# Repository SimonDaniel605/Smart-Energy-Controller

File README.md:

# Smart-Energy-Controller
A modular STM32-based smart energy monitoring and load control system with wireless connectivity, real-time power measurement, and remote switching.

## Overview

The Smart Energy Controller enables real-time monitoring of electrical consumption and wireless control of connected loads. The system is designed to support intelligent energy management through distributed monitoring, remote switching and centralised control.

- **Energy Monitoring:** Measurement of voltage, current, power, power factor and energy consumption.
- **Remote Switching:** Wireless control of connected electrical loads.
- **Real-Time Data:** Continuous transmission of electrical measurements.
- **Energy Management:** Automated load scheduling and power consumption optimisation.
- **Scalability:** Multiple controllers connected to a central monitoring system.
- **Remote Access:** Monitoring and control through a mobile device.

## Project Structure

```text
Smart-Energy-Controller/
├── Docs/
├── Firmware/
└── Hardware/
```

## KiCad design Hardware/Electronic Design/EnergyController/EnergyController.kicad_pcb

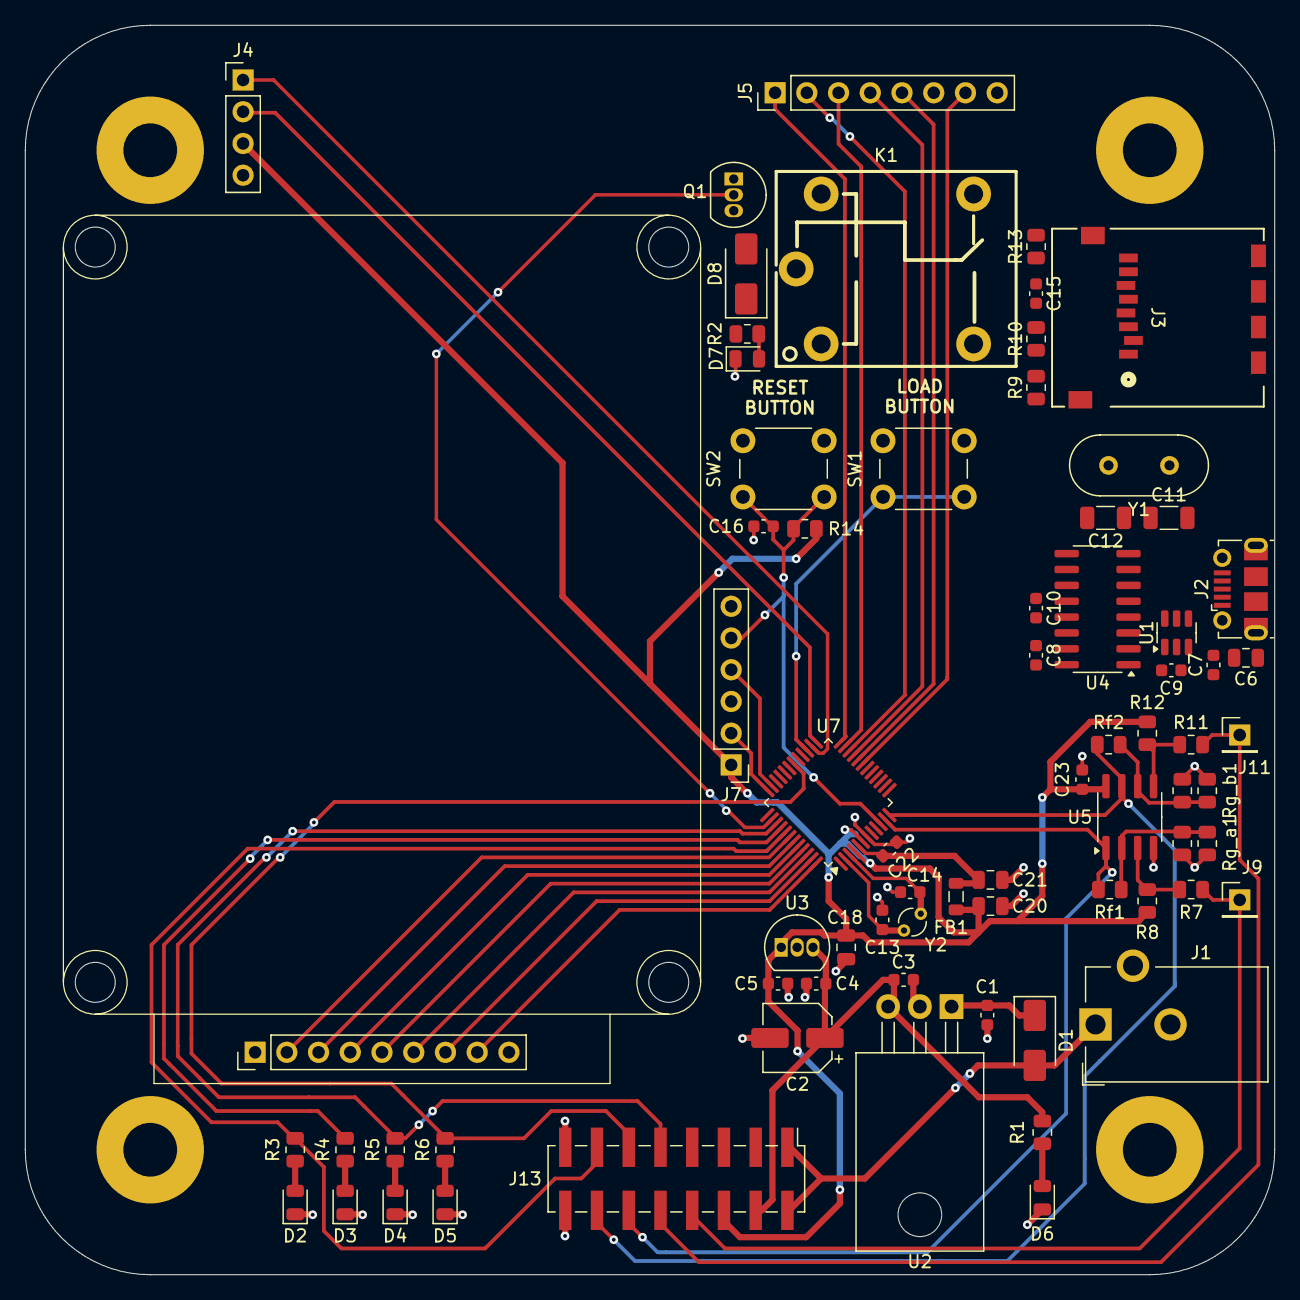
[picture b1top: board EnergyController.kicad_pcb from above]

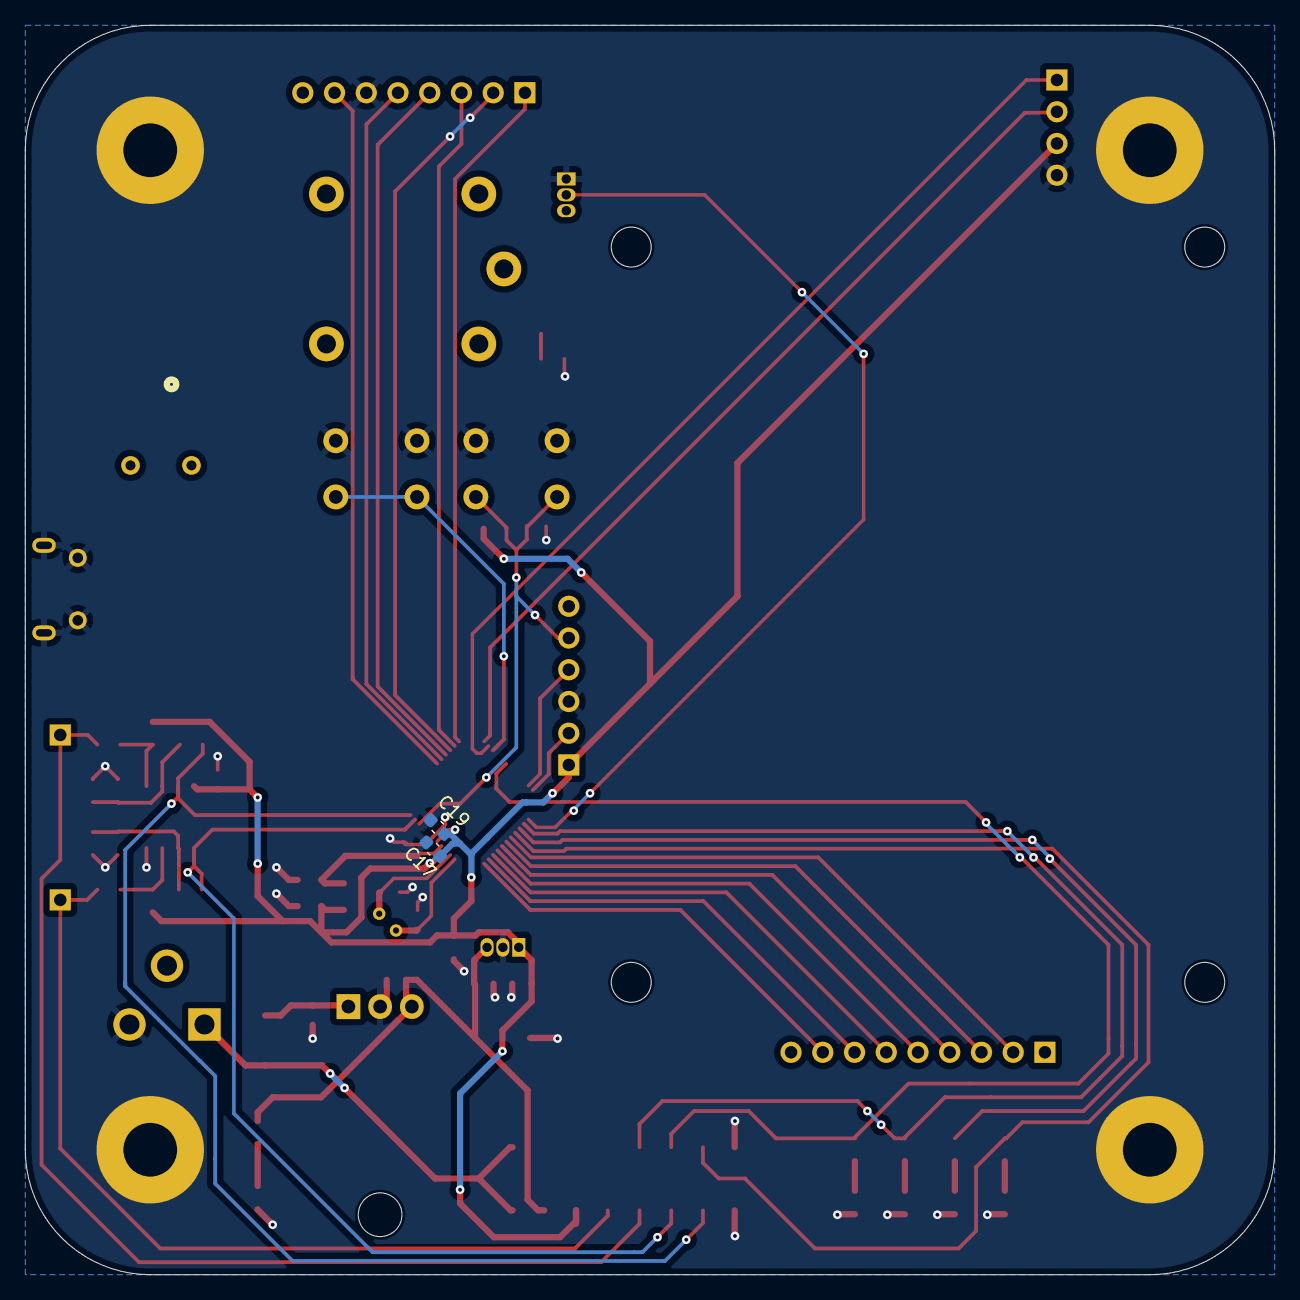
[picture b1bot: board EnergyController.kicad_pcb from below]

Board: 2 copper layers, 100.0 x 100.0 mm, 82 parts (2 on the bottom side), 61 nets.

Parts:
C1, C3, C4, C5, C7, C8, C9, C10, C15, C16, C17, C19, C23: 100n; C_0603_1608Metric
C2: 10u; CP_Elec_5x5.4
C6, C18: 10u; C_0805_2012Metric
C11, C12: 22p; C_1206_3216Metric
C13, C14: 20p; C_0603_1608Metric
C20, C21: 1u; C_0805_2012Metric
C22: 10n; C_0603_1608Metric
D1, D8: 1N4007; D_SMA
D2, D3, D4, D5, D6, D7: LED; LED_0805_2012Metric
FB1: 120R; L_0805_2012Metric
H1, H2, H3, H4: MountingHole_Pad; MountingHole_4.3mm_M4_Pad
H5, H6, H7, H8: MountingHole; MountingHole_3.2mm_M3
J1: Barrel_Jack; BarrelJack_CUI_PJ-102AH_Horizontal
J2: USB_OTG; USB_Micro-B_Molex-105017-0001
J3: 112A-TAAR-R03; CONN8_-TAAR-R03_ATT
J4: Conn_01x04_Pin; PinHeader_1x04_P2.54mm_Vertical
J5: Conn_01x08_Pin; PinHeader_1x08_P2.54mm_Vertical
J6: Conn_01x09_Pin; PinHeader_1x09_P2.54mm_Vertical
J7: Conn_01x06_Pin; PinHeader_1x06_P2.54mm_Vertical
J9, J11: Conn_01x01_Pin; PinHeader_1x01_P2.54mm_Vertical
J13: Conn_02x08; PinHeader_2x08_P2.54mm_Vertical_SMD
K1: Relay_SPDT; RELAY-TH_SRD-XXVDC-XL-C
Q1: 2N7000; TO-92_Inline
R1, R2, R3, R4, R5, R6: R; R_0805_2012Metric
R7, R11, R14: 10k; R_0805_2012Metric
R8, R12: 33k; R_0805_2012Metric
R9, R10, R13: 100k; R_0805_2012Metric
Rf1, Rf2: 10k; R_0805_2012Metric
Rg_a1: 10k; R_0805_2012Metric
Rg_a2: 68k; R_0805_2012Metric
Rg_b1: 10k; R_0805_2012Metric
Rg_b2: 68k; R_0805_2012Metric
SW1, SW2: SW_Push; SW_PUSH_6mm
U1: SRV05-4; SOT-23-6
U2: L7805; TO-220-3_Horizontal_TabDown
U3: L78L33_TO92; TO-92_Inline
U4: CH340G; SOIC-16_3.9x9.9mm_P1.27mm
U5: MCP602; SOIC-8_3.9x4.9mm_P1.27mm
U7: STM32G031C6Tx; LQFP-48_7x7mm_P0.5mm
Y1: 12 MHz; Crystal_HC49-U_Vertical
Y2: 32.768 kHz; Crystal_DS26_D2.0mm_L6.0mm_Vertical

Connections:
+3.3V: C5.1, C15.1, C17.1, C18.1, C19.1, C20.1, C23.1, FB1.1, J3.4 (VDD), J4.3, J5.8, J7.1, J13.6, R8.1, R9.1, R10.1, R12.2, R13.1, R14.1, U3.1 (VO), U5.8 (V+), U7.4 (VBAT), U7.6 (VDD)
+3.3VA: C21.1, C22.1, FB1.2, U7.5 (VREF+)
+5V: C2.1, C3.1, C4.1, D8.1 (K), J13.4, R1.1, U2.3 (OUT), U3.3 (VI)
+9V: D1.2 (A), J1.1, J13.1, J13.2
/LSE_IN: C13.1, U7.2 (PC14), Y2.1
/LSE_OUT: C14.1, U7.3 (PC15), Y2.2
ADC_Current: J13.14, Rf2.2, U5.7, U7.12 (PA1)
ADC_Voltage: J13.12, Rf1.2, U5.1, U7.11 (PA0)
COL1: J6.4, U7.44 (PB5)
COL2: J6.2, U7.42 (PB3)
COL3: J6.6, U7.46 (PB7)
CurrentSignal: J11.1, J13.10, R11.1
GND: C1.2, C2.2, C3.2, C4.2, C5.2, C6.1, C7.1, C8.1, C9.1, C11.2, C12.2, C13.2, C14.2, C15.2, C16.2, C17.2, C18.2, C19.2, C20.2, C21.2, C22.2, C23.2, D2.1 (K), D3.1 (K), D4.1 (K), D5.1 (K), D6.1 (K), D7.1 (K), H1.1, H2.1, H3.1, H4.1, J1.2, J2.5 (GND), J2.6 (Shield), J3.6 (VSS), J3.9 (GND), J3.11 (GND), J3.13 (GND), J3.14 (GND), J4.4, J5.6, J7.3, J13.15, J13.16, Q1.1 (S), Rg_a1.2, Rg_a2.2, Rg_b1.2, Rg_b2.2, SW1.1, SW2.1, U1.2 (VN), U2.2 (GND), U3.2 (GND), U4.1 (GND), U5.4 (V-), U7.7 (VSS)
LOAD: J13.13, R3.1, U7.41 (PD3)
LOAD_Extra: Q1.2 (G), U7.38 (PD0)
NRST: C16.1, J7.5, R14.2, SW2.2, U7.10 (PF2)
unnamed: C1.1, D1.1 (K), U2.1 (IN)
unnamed: D2.2 (A), R3.2
unnamed: D3.2 (A), R4.2
unnamed: D4.2 (A), R5.2
unnamed: D5.2 (A), R6.2
unnamed: D6.2 (A), R1.2
unnamed: D7.2 (A), R2.1
unnamed: D8.2 (A), Q1.3 (D)
unnamed: J2.3 (D+), U1.6 (IO4), U4.5 (UD+)
unnamed: J2.2 (D-), U1.4 (IO3), U4.6 (UD-)
unnamed: C9.2, U4.4 (V3)
unnamed: C11.1, U4.7 (XI), Y1.1
unnamed: C12.1, U4.8 (XO), Y1.2
unnamed: C10.2, U4.13 (~DTR)
unnamed: R7.2, R8.2, U5.3 (+)
unnamed: Rf1.1, Rg_a1.1, Rg_a2.1, U5.2 (-)
unnamed: R11.2, R12.1, U5.5 (+)
unnamed: Rf2.1, Rg_b1.1, Rg_b2.1, U5.6 (-)
OLED_SCL: J4.2, U7.25 (PB13)
OLED_SDA: J4.1, U7.26 (PB14)
Power_High: J13.11, R6.1, U7.30 (PC6)
RFID_MISO: J5.4, U7.21 (PB2)
RFID_MOSI: J5.3, U7.23 (PB11)
RFID_RQ: J5.5, U7.20 (PB1)
RFID_RST: J5.7, U7.19 (PB0)
RFID_SCK: J5.2, U7.22 (PB10)
RFID_SDA: J5.1, U7.24 (PB12)
ROW1: J6.3, U7.43 (PB4)
ROW2: J6.8, U7.48 (PB9)
ROW3: J6.7, U7.47 (PB8)
ROW4: J6.5, U7.45 (PB6)
RX: J13.5, U4.2 (TXD), U7.14 (PA3)
SD_CS: J3.2 (CD/DAT3), R9.2, U7.15 (PA4)
SD_MISO: J3.7 (DAT0), R13.2, U7.17 (PA6)
SD_MOSI: J3.3 (CMD), R10.2, U7.18 (PA7)
SD_SCK: J3.5 (CLK), U7.16 (PA5)
SWCLK: J7.2, U7.36 (PA14)
SWDIO: J7.4, U7.35 (PA13)
TOGGLE: J13.7, SW1.2, U7.27 (PB15)
TX: J13.3, U4.3 (RXD), U7.13 (PA2)
Units_Low: R4.1, U7.40 (PD2)
V_USB: C6.2, C7.2, C8.2, J2.1 (VBUS), U1.5 (VP), U4.16 (VCC)
VoltageSignal: J9.1, J13.8, R7.1
Wh_Ticker: J13.9, R5.1, U7.39 (PD1)
uC_Reset: C10.1, U7.28 (PA8)
